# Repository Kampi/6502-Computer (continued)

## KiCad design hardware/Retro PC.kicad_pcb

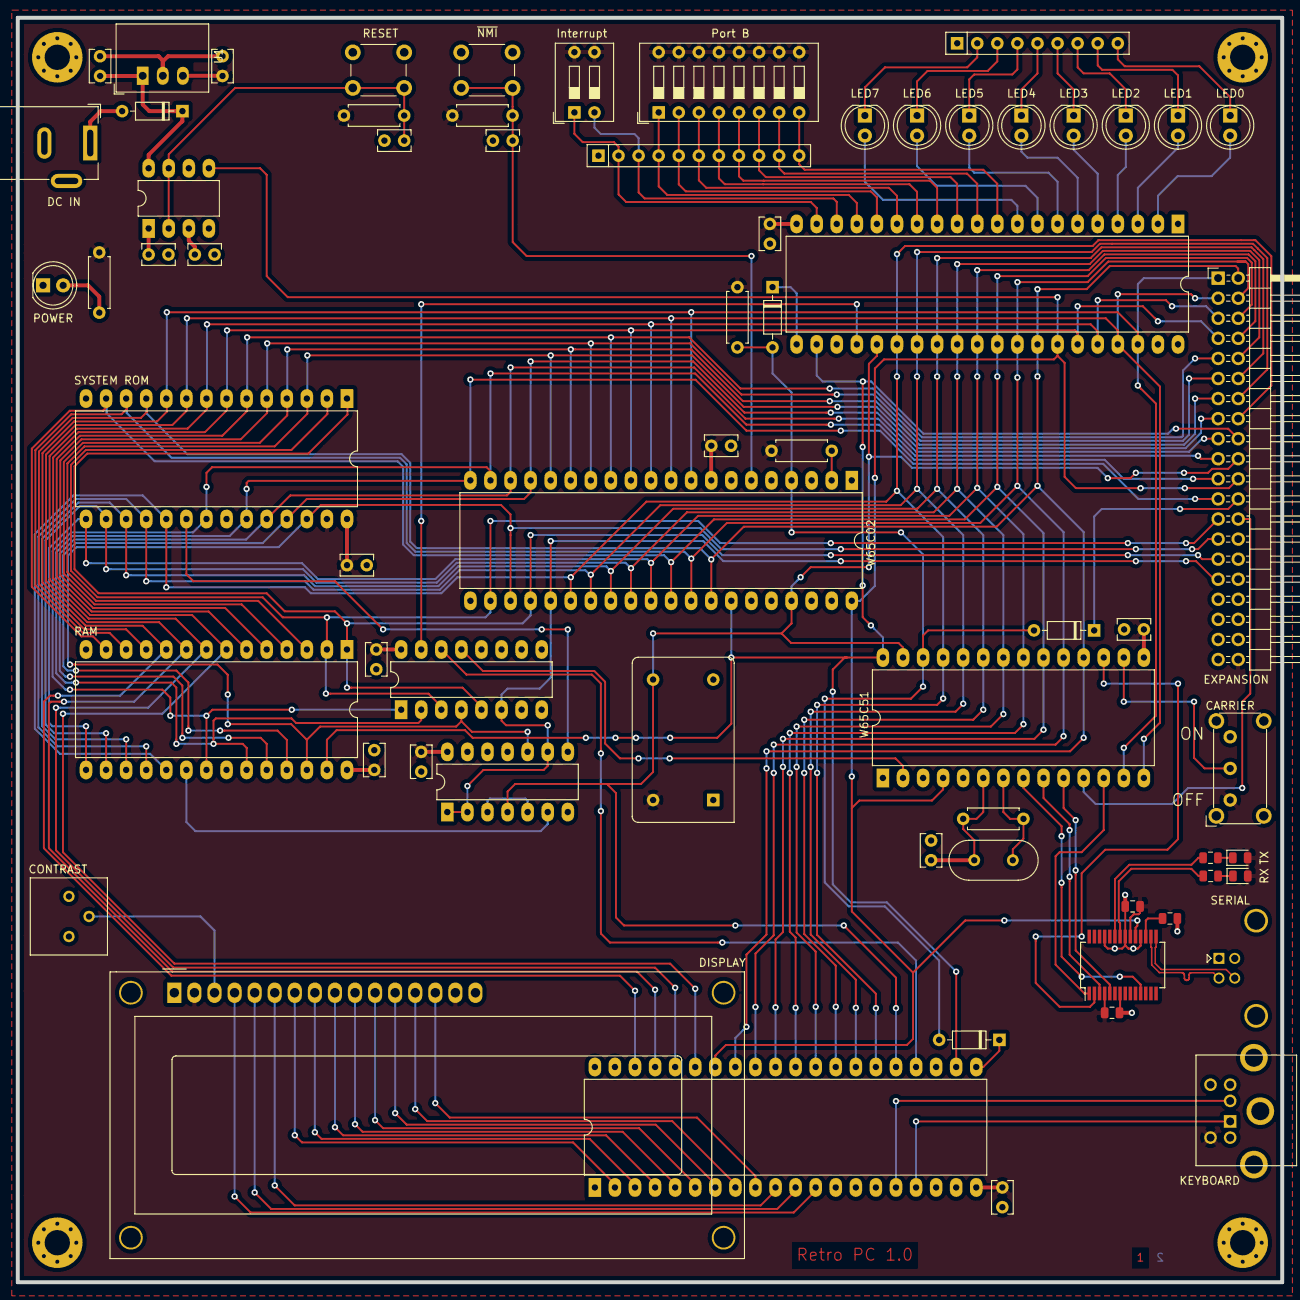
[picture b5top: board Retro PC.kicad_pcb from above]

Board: 2 copper layers, 160.0 x 160.0 mm, 67 parts (0 on the bottom side), 103 nets.

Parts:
C1, C2, C3, C4, C5, C6, C7, C8, C10, C11, C12, C13, C17, C18: 100nF; C_Rect_L4.0mm_W2.5mm_P2.50mm
C9: 330nF; C_Rect_L4.0mm_W2.5mm_P2.50mm
C14, C15, C16: 100nF; C_0805_2012Metric
D0: LED0; LED_D5.0mm
D1: LED1; LED_D5.0mm
D2: LED2; LED_D5.0mm
D3: LED3; LED_D5.0mm
D4: LED4; LED_D5.0mm
D5: LED5; LED_D5.0mm
D6: LED6; LED_D5.0mm
D7: LED7; LED_D5.0mm
D8, D9, D14: SD103A; D_DO-35_SOD27_P7.62mm_Horizontal
D10: 1N4148; D_DO-35_SOD27_P7.62mm_Horizontal
D11: TX; LED_0805_2012Metric
D12: RX; LED_0805_2012Metric
D13: POWER; LED_D5.0mm
DS1: DISPLAY; WC1602A
IC1: 74HC00; DIP-14_W7.62mm_LongPads
IC2: W65C02; DIP-40_W15.24mm_LongPads
IC3: 74HC138; DIP-16_W7.62mm_LongPads
IC4: SYSTEM ROM; DIP-28_W15.24mm_LongPads
IC5: RAM; DIP-28_W15.24mm_LongPads
IC6, IC10: W65C22; DIP-40_W15.24mm_LongPads
IC7: W65C51; DIP-28_W15.24mm_LongPads
IC8: TL7702A; DIP-8_W7.62mm_LongPads
IC9: FT232RL; SSOP-28_5.3x10.2mm_P0.65mm
R1, R3, R5, R9: 10k; R_Axial_DIN0207_L6.3mm_D2.5mm_P7.62mm_Horizontal
R4: 1M; R_Axial_DIN0207_L6.3mm_D2.5mm_P7.62mm_Horizontal
R6, R7: 1k; R_0805_2012Metric
R8: 470; R_Axial_DIN0207_L6.3mm_D2.5mm_P7.62mm_Horizontal
RN1: 10k; R_Array_SIP11
RN2: 470; R_Array_SIP9
RV1: 10k; Bourns_3386T_Vertical
SW1: RESET; SW_PUSH_6mm_H4.3mm
SW2: Interrupt; SW_DIP_SPSTx02_Slide_9.78x7.26mm_W7.62mm_P2.54mm
SW3: Port B; SW_DIP_SPSTx08_Slide_9.78x22.5mm_W7.62mm_P2.54mm
SW4: ~NMI; SW_PUSH_6mm_H4.3mm
SW5: CARRIER; SW_E-Switch_EG1224_SPDT_Angled
U1: R-785.0-1.0; Converter_DCDC_RECOM_R-78E-0.5_THT
X1: DC IN; BarrelJack_Wuerth_6941xx301002
X2: SERIAL; USB-B_TE_2923042_Horizontal
X3: EXPANSION; PinHeader_2x20_P2.54mm_Horizontal
X4: KEYBOARD; Mini-DIN_TE_Female_6Pin_2rows
XTAL1: 1MHz; Oscillator_DIP-14
XTAL2: 1.8432MHz; Crystal_HC49-U_Vertical

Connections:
+5V: C1.1, C2.1, C3.1, C4.1, C5.1, C6.1, C7.1, C10.1, C15.1, C16.1, C18.1, D11.2, D12.2, DS1.2, DS1.15, IC1.14, IC2.8, IC3.16, IC4.27, IC4.28, IC5.28, IC6.20, IC7.15, IC9.4, IC9.20, IC10.20, R1.2, R3.1, R5.1, R8.1, R9.1, SW2.3, SW2.4, SW3.9, SW3.10, SW3.11, SW3.12, SW3.13, SW3.14, SW3.15, SW3.16, SW5.1, U1.3, X3.40, X4.5, XTAL1.14
+VDC: C9.1, D10.1, IC8.8, U1.1
/IO/A0: IC2.9, IC4.10, IC5.10, IC6.38, IC7.13, IC10.38, X3.1
/IO/A1: IC2.10, IC4.9, IC5.9, IC6.37, IC7.14, IC10.37, X3.3
/IO/A2: IC2.11, IC4.8, IC5.8, IC6.36, IC10.36, X3.5
/IO/A3: IC2.12, IC4.7, IC5.7, IC6.35, IC10.35, X3.7
/IO/A4: IC2.13, IC4.6, IC5.6, X3.9
/IO/A5: IC2.14, IC4.5, IC5.5, X3.11
/IO/A6: IC2.15, IC4.4, IC5.4, X3.13
/IO/A7: IC2.16, IC4.3, IC5.3, X3.15
/IO/A8: IC2.17, IC4.25, IC5.25, X3.17
/IO/A9: IC2.18, IC4.24, IC5.24, X3.19
/IO/A10: IC2.19, IC3.1, IC4.21, IC5.21, X3.21
/IO/A11: IC2.20, IC3.2, IC4.23, IC5.23, X3.23
/IO/A12: IC2.22, IC3.3, IC4.2, IC5.2, X3.25
/IO/A13: IC1.10, IC2.23, IC3.4, IC4.26, IC5.26, X3.27
/IO/A14: IC2.24, IC3.5, IC4.1, IC5.1, X3.29
/IO/A15: IC1.1, IC1.2, IC1.9, IC2.25, IC3.6, X3.31
/IO/CB1: IC6.18, RN1.3, SW2.2
/IO/CB2: IC6.19, RN1.2, SW2.1
/IO/Clock: IC1.4, IC2.37, IC6.25, IC7.27, IC10.25, X3.20, XTAL1.8
/IO/D0: IC2.33, IC4.11, IC5.11, IC6.33, IC7.18, IC10.33, X3.2
/IO/D1: IC2.32, IC4.12, IC5.12, IC6.32, IC7.19, IC10.32, X3.4
/IO/D2: IC2.31, IC4.13, IC5.13, IC6.31, IC7.20, IC10.31, X3.6
/IO/D3: IC2.30, IC4.15, IC5.15, IC6.30, IC7.21, IC10.30, X3.8
/IO/D4: IC2.29, IC4.16, IC5.16, IC6.29, IC7.22, IC10.29, X3.10
/IO/D5: IC2.28, IC4.17, IC5.17, IC6.28, IC7.23, IC10.28, X3.12
/IO/D6: IC2.27, IC4.18, IC5.18, IC6.27, IC7.24, IC10.27, X3.14
/IO/D7: IC2.26, IC4.19, IC5.19, IC6.26, IC7.25, IC10.26, X3.16
/IO/PA0: D0.2, IC6.2
/IO/PA1: D1.2, IC6.3
/IO/PA2: D2.2, IC6.4
/IO/PA3: D3.2, IC6.5
/IO/PA4: D4.2, IC6.6
/IO/PA5: D5.2, IC6.7
/IO/PA6: D6.2, IC6.8
/IO/PA7: D7.2, IC6.9
/IO/PB0: IC6.10, RN1.11, SW3.8
/IO/PB1: IC6.11, RN1.10, SW3.7
/IO/PB2: IC6.12, RN1.9, SW3.6
/IO/PB3: IC6.13, RN1.8, SW3.5
/IO/PB4: IC6.14, RN1.7, SW3.4
/IO/PB5: IC6.15, RN1.6, SW3.3
/IO/PB6: IC6.16, RN1.5, SW3.2
/IO/PB7: IC6.17, RN1.4, SW3.1
/IO/R~W: IC2.34, IC5.27, IC6.22, IC7.28, IC10.22, X3.18
/IO/~CarrierDetect: IC7.16, SW5.2
/IO/~IRQ: D9.1, X3.24
/IO/~NMI: C17.1, IC2.6, R9.2, SW4.2
/IO/~RESET: IC2.40, IC6.34, IC7.4, IC8.5, IC9.19, IC10.34, X3.22
/IO/~TerminalReady: IC7.11, X3.26
/LCD / PS2/LCD0: DS1.6, IC10.10
/LCD / PS2/LCD1: DS1.5, IC10.11
/LCD / PS2/LCD2: DS1.4, IC10.12
/LCD / PS2/LCD3: DS1.7, IC10.2
/LCD / PS2/LCD4: DS1.8, IC10.3
/LCD / PS2/LCD5: DS1.9, IC10.4
/LCD / PS2/LCD6: DS1.10, IC10.5
/LCD / PS2/LCD7: DS1.11, IC10.6
/LCD / PS2/LCD8: DS1.12, IC10.7
/LCD / PS2/LCD9: DS1.13, IC10.8
/LCD / PS2/LCD10: DS1.14, IC10.9
/LCD / PS2/PS20: IC10.16, X4.2
/LCD / PS2/PS21: IC10.17, X4.1
/Processor/CTS: IC7.9, IC9.3
/Processor/RxD: IC7.12, IC9.1
/Processor/~CS_ACIA: IC3.13, IC7.2
/Processor/~CS_VIA_1: IC3.15, IC6.24
/Processor/~CS_VIA_2: IC3.14, IC10.24
/Processor/~IRQ_ACIA: D8.2, D9.2, D14.2, IC2.4, IC7.26, R1.1
/Processor/~IRQ_VIA_1: D8.1, IC6.21
/Processor/~IRQ_VIA_2: D14.1, IC10.21
/Processor/~ModemReady: IC7.17, IC9.2
/USB/CTS: IC7.8, IC9.11
/USB/D+: IC9.15, X2.3
/USB/D-: IC9.16, X2.2
/USB/RxD: IC7.10, IC9.5
GND: C1.2, C2.2, C3.2, C4.2, C5.2, C6.2, C7.2, C8.2, C9.2, C10.2, C11.2, C12.2, C13.2, C14.1, C15.2, C16.2, C17.2, C18.2, D13.1, DS1.1, DS1.16, IC1.7, IC2.21, IC3.8, IC4.14, IC4.22, IC5.14, IC5.22, IC6.1, IC6.23, IC7.1, IC7.3, IC8.4, IC9.7, IC9.18, IC9.21, IC9.25, IC10.1, IC10.23, RN1.1, RN2.1, RV1.1, SW1.1, SW4.1, SW5.3, U1.2, X1.2, X2.4, X2.5, X3.39, X4.4, X4.7, XTAL1.7
unnamed: C8.1, IC7.6, R4.2, XTAL2.1
unnamed: C11.1, IC8.2, IC8.7, R5.2, SW1.2
unnamed: C12.1, IC8.3
unnamed: C13.1, IC8.1
unnamed: C14.2, IC9.17
unnamed: D0.1, RN2.9
unnamed: D1.1, RN2.8
unnamed: D2.1, RN2.7
unnamed: D3.1, RN2.6
unnamed: D4.1, RN2.5
unnamed: D5.1, RN2.4
unnamed: D6.1, RN2.3
unnamed: D7.1, RN2.2
unnamed: D10.2, X1.1
unnamed: D11.1, R6.1
unnamed: D12.1, R7.1
unnamed: D13.2, R8.2
unnamed: DS1.3, RV1.2
unnamed: IC1.3, IC1.5
unnamed: IC1.6, IC5.20
unnamed: IC1.8, IC4.20
unnamed: IC2.2, R3.2
unnamed: IC7.7, R4.1, XTAL2.2
unnamed: IC9.22, R7.2
unnamed: IC9.23, R6.2

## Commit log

2019-10-08 Add license
2019-10-08 Create Development branch
2019-10-13 Working on layout
2019-10-15 Working on Schematic
2019-10-17 First version of the layout
2019-10-18 Replace LCD
2019-10-18 Add BOM and Schematics
2019-10-18 Add mouser shopping cart
2019-10-18 Add documentation
2019-10-18 Finalize schematic and layout. Add switch for carrier detect
2019-10-18 Remove old files
2019-10-18 Update README from master
2019-10-20 Add Timer extension
2019-10-20 Update documentation
2019-10-20 Move files
2019-10-20 Remove files
2019-11-01 Rename directory
2019-11-06 Add change log
2019-11-07 Add pull-up resistor for RESET
2019-11-07 Change location of R3 reference
2019-11-08 Remove old BOM
2019-11-08 Add switch to select between oscillator as clock and manual clock source
2019-11-11 Add switch for clock selection
2019-11-21 Change C8 to 30 pF
2019-11-24 Rework hardware for IRQ, change some routing
2019-11-25 Update changelog
2019-11-25 Improve routing, add some datasheet recommendations
2019-11-25 Remove timer extension
2019-11-25 Optimize routing
2019-12-01 Optimize routing, add RDY and SYNC to expansion header
2019-12-01 Add WDC documentation
2019-12-01 Add branch for board extensions
2019-12-01 Remove README and Changelog
2019-12-01 Fix wrong image path in README
2019-12-02 Add note to IRQ schematic
2019-12-02 Add board design template
2019-12-02 Update README and Changelog
2019-12-02 Add Power Supply board for the new retro computer design
2019-12-02 Move WDC documentation into 'datasheets' folder
2019-12-02 Add Processor Board
2019-12-02 Update power supply
2019-12-02 Update processor board routing
2019-12-02 Improve routing
2019-12-02 Add 3D drawings
2019-12-03 Add IO board
2019-12-03 Update 3D drawings
2019-12-03 Remove old shopping cart
2019-12-03 Update processor board
2019-12-03 Rename PortB and the interrupt DIP switch
2019-12-03 Remove old docs
2019-12-03 Rename NMI push button
2019-12-03 Working on 3D drawing
2019-12-03 Working on hardware
2020-01-03 Move CS signals for peripheral devices to not(CS) pins
2020-01-03 Replace RN2 with 390 Ohms restistor network
2020-01-10 Add VP signal to expansion header, optimize routing
2020-01-24 Change compiler and update first example
2020-01-24 Remove WDC toolchain documentation
2020-01-24 Working on PCB
2020-01-24 Add linker script
2020-01-24 Add Arduino bus analyzer firmware
2020-01-24 Update MAKEFILE
2020-01-24 Add phony targets to makefile
2020-02-09 Fix wrong mail adress in README
2020-02-09 Add pull up resistors for PS/2, add LCD backlight switch
2020-03-17 Misc: - Update Changelog and README - Remove old files - Update documenation BOM: - Fix different wrong part numbers
    Software:
    - Rework MAKEFILE
    - Update linker script with zero page
    - Add RAM layout description
    - Working on software examples
    Schematic:
2020-04-05 Misc: - Update README - Add 74HC138 datasheet - Update board image - Add layout for website tutorial
2020-10-11 Hardware: - Add pull up resistor for PB
    Documentation:
    - Add more datasheets
    - Update documentation
    Misc:
    - Rename CHANGELOG
    - Remove old files
2021-05-10 Release 0.2
2021-05-10 Initialize branch
2021-05-10 Update project
2024-10-12 Fix grid issues, fix missing libraries, replace FT232 with FT231
2024-10-12 Apply gitignore
2024-10-12 Fix swapped DM and DP, add missing datasheets, remove Mouser property
